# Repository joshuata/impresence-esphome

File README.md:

# Presence Sensor

An open-source, ESPHome-based room presence sensor built around the Hi-Link HLK-LD2460 mmWave radar and a Seeed Studio XIAO ESP32-S3. The base device detects human presence, even when people are sitting still, and reports it to Home Assistant. Optional add-ons extend it with ambient light and CO₂ sensing.

> **Status:** early development. Hardware and firmware are not yet finalized.

<!-- TODO: hero photo of the assembled device -->

## Features

- mmWave presence detection (HLK-LD2460)
- Native Home Assistant integration through ESPHome
- Wi-Fi setup over USB or Bluetooth (Improv), with no code editing required
- Browser-based flashing, no toolchain needed
- Over-the-air updates
- Optional add-ons:
  - Ambient light sensor
  - CO₂ sensor
- Custom PCB and 3D-printable enclosure, with source files included

## Bill of materials

### Base device

| Qty | Part | Notes |
|----:|------|-------|
| 1 | Seeed Studio XIAO ESP32-S3 | |
| 1 | Hi-Link HLK-LD2460 mmWave radar | |
| 1 | Custom PCB, assembled | Order it with assembly; see [1. PCB](#1-pcb) |
| 1 | 3D-printed enclosure | See [`hardware/enclosure`](hardware/enclosure) |
| 1 | USB-C cable + 5 V power supply | |
| 1 | PCB parts (radar sockets, Qwiic socket, LDO, passives) | Only if you assemble the PCB yourself. Full list in [`hardware/pcb/presence-pcb-bom.csv`](hardware/pcb/presence-pcb-bom.csv) |
| 4 | M2.5 screws + heat-set inserts | Length TBD with the case |

### Optional add-ons

| Add-on | Part | Notes |
|--------|------|-------|
| Ambient light | Adafruit VEML7700 Lux Sensor, STEMMA QT (5378) | Plugs into the Qwiic chain |
| CO₂ | Adafruit SCD-40 breakout (5187) | Plugs into the Qwiic chain |

## Building

### 1. PCB

The fabrication files are in [`hardware/pcb`](hardware/pcb):

| File | What it's for |
|------|---------------|
| `presence-pcb-gerbers.zip` | Gerber and drill files. Upload this to any PCB maker |
| `presence-pcb-bom.csv` | Every part on the board, with manufacturer and LCSC part numbers |
| `presence-pcb-bom-jlcpcb.csv` | Assembly BOM in JLCPCB's format |
| `presence-pcb-cpl-jlcpcb.csv` | Pick-and-place (CPL) file in JLCPCB's format |

The board has two layers and is 53.5 × 57.955 mm, 1.6 mm thick. It uses 0.2 mm minimum tracks and clearances and 0.3 mm via drills, which any standard PCB service can make. Every part is on the top side.

#### Ordering from JLCPCB with assembly

JLCPCB can build the board with everything fitted except the XIAO, which you solder yourself. The optional parts (R1, R2, J4) are left off; see [Optional parts](#optional-parts).

1. On [jlcpcb.com](https://jlcpcb.com), start a PCB order and upload `presence-pcb-gerbers.zip`. Check that it detects 2 layers and a size of about 53.5 × 58 mm.
2. Set the PCB options:
   - **Base material:** FR-4
   - **Layers:** 2
   - **PCB thickness:** 1.6 mm
   - **Surface finish:** lead-free HASL or ENIG
   - **Quantity:** however many bare boards you want
   - Leave the other options at their defaults. Some colours and finishes aren't offered with Economic assembly; the site greys those out.
3. Turn on **PCB Assembly** and set:
   - **PCBA type:** Economic
   - **Assembly side:** Top side
   - **PCBA quantity:** the number of boards to assemble. The minimum is 2.
   - **Confirm parts placement:** yes. A JLCPCB engineer checks the part orientations and sends them to you to approve before assembly, for a small fee. It's worth it until the files have been proven on a real order.
4. Upload `presence-pcb-bom-jlcpcb.csv` as the BOM and `presence-pcb-cpl-jlcpcb.csv` as the CPL (pick-and-place) file.
5. On the parts page, check that every line matched the LCSC part number in the file. There should be eight lines:
   - **Basic parts:** C1–C5, FB1
   - **Extended parts:** U2, J1, J2, J3. Each unique extended part adds a feeder-loading fee.
   - **J1 and J2:** the radar sockets are through-hole, so JLCPCB solders them by hand and adds a small through-hole fee. To solder them yourself instead, untick them and buy HCTL PM200-2-04-Z-4.3 and PM200-2-02-Z-4.3. Any substitute must be 4.3 mm tall (`pcb_socket_h`), or the radar won't line up with the case.
   - **Out-of-stock parts:** choose one with the same value, rating and footprint. For J3, use only the JST BM04B-SRSS-TB or an exact equivalent: the case is shaped around its height.
6. In the placement preview, check that every part sits on its pads and that the polarised parts point the right way:
   - **J1:** the 2×4 socket lies along its two columns of four holes. The CPL file already corrects for JLCPCB's model being drawn at 90° to the footprint
   - **U2:** pin 1
   - **J3:** the four contacts on the small pads and the mounting tabs on the two large ones
7. Add the order to your cart and check out. JLCPCB asks for a product description for customs; pick the closest one.

The Gerber zip works with any other PCB maker too. Other assembly services need their own BOM and CPL formats; build them from `presence-pcb-bom.csv`.

#### After the boards arrive

1. **XIAO ESP32-S3 (U1):** solder it flush, with its castellated edges on the pads, or on pin headers. Only the 14 edge pins are used. There's no copper under the XIAO's bottom pads, so don't solder those.
2. **Check before powering:** before powering the first board, check the radar socket pinout against a module, following [Wiring](hardware/README.md#wiring). In short: JP103 pin 1 (5 V) is the bottom pin of the column nearest the board edge.

#### Optional parts

| Ref | Part | When to fit it |
|-----|------|----------------|
| R1, R2 | 4.7 kΩ 0805 resistors (I²C pull-ups) | Only for a Qwiic breakout without its own pull-ups. The Adafruit breakouts have them |
| J4 | 1×4 2.54 mm header | To solder an I²C cable instead of using the Qwiic socket |

### 2. Enclosure

TODO: print settings (material, layer height, supports, infill) and orientation.

### 3. Assembly

TODO: mounting the PCB, radar orientation, and installing add-ons.

## Flashing

### Option A: Browser (recommended)

TODO: link to the ESP Web Tools install page. Connect the device over USB, click **Install**, then enter your Wi-Fi credentials when prompted.

### Option B: ESPHome Dashboard / CLI

Requires ESPHome TBD or newer, the first release with the [`ld2460`](https://next.esphome.io/components/sensor/ld2460/) component.

```bash
pip install esphome
esphome run firmware/presence.yaml
```

TODO: adopting the device in the ESPHome Dashboard.

## Wi-Fi setup

TODO: Improv over serial/BLE and fallback access point instructions.

## Home Assistant

TODO: discovery, exposed entities, and suggested automations.

## Enabling add-ons

TODO: how to include the add-on packages in `firmware/presence.yaml`.

## Repository layout

| Path | Contents |
|------|----------|
| `firmware/` | ESPHome configuration and add-on packages |
| `hardware/pcb/` | Autodesk Fusion PCB design and fabrication exports |
| `hardware/enclosure/` | Autodesk Fusion enclosure design and printable files |
| `docs/` | Images, wiring diagrams, web installer |

## Made for ESPHome

This project aims to meet the [Made for ESPHome](https://esphome.io/guides/made_for_esphome/) requirements. Progress against the [checklist](https://github.com/esphome/devices.esphome.io/blob/main/.github/made-for-esphome-checklist.md) is tracked in the project issues.

## Contributing

Issues and pull requests are welcome. If you use an AI coding agent, it should follow [`AGENTS.md`](AGENTS.md).

## License

- **Firmware, software, and documentation:** [GNU General Public License v3.0 or later](LICENSE) (`GPL-3.0-or-later`).
- **Hardware designs** (everything under `hardware/`: PCB, enclosure, and their fabrication exports): [CERN Open Hardware Licence v2 – Strongly Reciprocal](LICENSE-HARDWARE) (`CERN-OHL-S-2.0`).

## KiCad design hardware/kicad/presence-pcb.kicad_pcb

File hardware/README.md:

# Hardware

The Autodesk Fusion project **Presence sensor** holds the mechanical source designs; Fusion exports are kept here so they are version controlled and usable without Fusion. The main PCB is a KiCad project in this folder (see `AGENTS.md`, Hardware).

| Path | Contents |
|------|----------|
| `fusion/` | Fusion source exports (`.f3d`; `.f3z` for designs with inserted, referenced components) |
| `kicad/` | KiCad 10 project for the main PCB: schematic, board, project symbol/footprint library and build scripts |
| `pcb/` | Fabrication outputs for the main PCB: Gerber + drill zip, BOM, JLCPCB assembly files |
| `enclosure/` | Print outputs for the case (once finalized) |

## Designs

| Design | What it is |
|--------|------------|
| `ld2460 Board` | HLK-LD2460 radar: board, headers, pins, keep-outs |
| `xiao-esp32s3` | Seeed XIAO ESP32-S3: board, pin holes, USB-C, keep-out |
| `adafruit-scd40` | Adafruit SCD-40 breakout (for later case variants) |
| `adafruit-veml7700` | Adafruit VEML7700 breakout (for later case variants) |
| `presence-skeleton` | Master layout for the radar + PCB prototype. Derives the radar and XIAO models and holds every case, PCB, mount and antenna dimension |

## Changing dimensions

The dimensions you're likely to change are named user parameters, and most others are derived from them or from the component models. In Fusion, open `presence-skeleton` and go to **Modify → Change Parameters**. Edit the value in the *User Parameters* section, and everything that depends on it updates. Parameters ending in `_Ref` come from the component models; change those in the component design instead. The case derives from the skeleton, so changes made there flow through to it. The KiCad PCB takes its outline, holes and part positions from the same values (in `kicad/scripts/build_board.py`), so update the script and rebuild the board after changing a layout parameter.

Values most people will want to check before printing are **bold**.

### Layout

| Parameter | Value | Description |
|-----------|-------|-------------|
| `pcb_thickness` | 1.6 mm | Main PCB thickness |
| **`pcb_socket_h`** | 4.3 mm | Height of the 2.0 mm female sockets the radar plugs into. Set to the part you buy |
| `pcb_margin` | 2 mm | PCB extends this far beyond the radar outline |
| `pcb_hole_inset` | 3 mm | PCB edge to mounting-hole centre |
| `pcb_pin_protrusion` | 2 mm | Through-hole pin length below the PCB |
| `layout_gap_radar_xiao` | 3 mm | Gap between the radar outline and the top of the XIAO |
| `xiao_side_offset` | 10 mm | XIAO shifted right (toward the antenna) to leave room on the left for a right-angle USB-C plug |

### Case

| Parameter | Value | Description |
|-----------|-------|-------------|
| `case_wall` | 2 mm | Wall thickness |
| `case_corner_r` | 3 mm | Outer corner radius |
| `case_margin` | 1 mm | Clearance from the PCB edge to the inner wall |
| **`case_radome_t`** | 1.4 mm | Wall thickness in front of the radar (community reports for 24 GHz; verify with a range test) |
| **`case_radome_gap`** | 2 mm | Radar antenna face to the inside of the front wall (1–3 mm) |
| **`case_bay_h`** | 12.5 mm | Cable bay below the PCB; sized for a right-angle USB-C plug |
| **`tol_clearance`** | 0.2 mm | General clearance between printed parts; tune for your printer |

### Fasteners

| Parameter | Value | Description |
|-----------|-------|-------------|
| `screw_clear_d` | 2.7 mm | M2.5 clearance hole in the PCB |
| **`insert_hole_d`** | 3.6 mm | Heat-set insert hole diameter. Inserts vary by brand; use your supplier's recommendation |
| **`insert_hole_h`** | 4 mm | Heat-set insert hole depth |
| `insert_boss_d` | 6.5 mm | Boss diameter around each insert |

### Wall mount (keyholes)

The back has two keyholes on the vertical centreline. Any accessory, such as a wedge or stand, that presents two #8 pan-head screw heads (or printed studs of the same shape) at this spacing can hold the case.

| Parameter | Value | Description |
|-----------|-------|-------------|
| **`mount_head_d`** | 7.9 mm | #8 pan-head diameter (ASME B18.6.3 nominal; measure yours) |
| **`mount_head_h`** | 2.8 mm | #8 pan-head height (nominal; measure yours) |
| `mount_shank_d` | 4.2 mm | #8 shank diameter |
| `mount_keyhole_spacing` | 40 mm | Keyhole centre-to-centre |
| `mount_slot_len` | 8 mm | Slot length above each entry hole |

### Hinge

| Parameter | Value | Description |
|-----------|-------|-------------|
| **`hinge_pin_d`** | 1.75 mm | Hinge pin: a piece of 1.75 mm filament or a metal pin |
| `hinge_knuckles` | 5 | Number of hinge knuckles |
| `hinge_clearance` | 0.3 mm | Knuckle and pin clearance |

### Wi-Fi / Bluetooth antenna

The XIAO's included flexible antenna sticks flat to the inside of the right-hand side wall. Its U.FL cable makes a 180° U-bend before reaching the XIAO, to take strain off the antenna joint.

| Parameter | Value | Description |
|-----------|-------|-------------|
| `ant_len` × `ant_w` × `ant_t` | 37.5 × 17.5 × 0.25 mm | Antenna size (measured) |
| `ant_cable_len` | 60 mm | U.FL cable length (measured) |
| `ant_bend_gap` | 6 mm | Spacing of the U-bend |
| `ant_drop` | 5 mm | Antenna centre below the radar centreline |
| `xiao_ufl_from_edge`, `xiao_ufl_from_centre` | 1.72, 4.73 mm | U.FL connector position on the XIAO (from Seeed's 3D model) |

### USB cable

| Parameter | Value | Description |
|-----------|-------|-------------|
| `usb_plug_w` × `usb_plug_h` | 12 × 6.5 mm | Straight USB-C plug body (measure your cable) |
| `usb_cable_d` | 4 mm | Cable diameter |
| `usb_cable_bend_r` | 10 mm | Minimum bend radius |

### Derived values (don't edit)

| Parameter | Value | Meaning |
|-----------|-------|---------|
| `z_antenna_face` | 8.0 mm | Radar antenna face above the PCB front |
| `case_front_inner` | 10.0 mm | Inside of the front wall above the PCB front |
| `pcb_back_clear` | 6.3 mm | Space behind the PCB: the largest of pin clearance, insert depth and the depth the antenna needs |
| `case_inner_depth` | 17.9 mm | Inside depth of the case |
| `case_inner_half_w`, `case_inner_top`, `case_inner_bottom` | 27.75, 19.0, 52.455 mm | Inner case extents from the radar centre |
| `ant_path_len` | 44.2 mm | Estimated antenna cable route |
| `ant_path_slack` | 15.8 mm | Spare cable. **Must stay ≥ 0**; adjust `ant_drop` if it goes negative |

At these values the case is about 59.5 × 75.5 × 21.3 mm (W × H × D).

## Main PCB

KiCad project `kicad/presence-pcb.kicad_pro`; two layers, 53.5 × 57.955 mm, 1.6 mm. The outline, the four M2.5 holes, the radar sockets and the XIAO position come from `presence-skeleton` (radar centre = origin, PCB front facing the room). Every part is on the front; the back carries only through-hole pins and a GND pour.

### Rebuilding

```sh
cd hardware/kicad
kicad-cli sch export netlist --format kicadsexpr -o /tmp/presence.net presence-pcb.kicad_sch
"/Applications/KiCad/KiCad.app/Contents/Frameworks/Python.framework/Versions/Current/bin/python3" \
  scripts/build_board.py /tmp/presence.net      # placement, routing, pours, silkscreen
scripts/export_fab.sh                           # ERC + DRC + parity, then hardware/pcb/*
```

`build_board.py` routes with its own small grid router, so the board is reproducible from the schematic without an autorouter. The custom footprints in `presence.pretty` come from `scripts/gen_footprints.py`.

### Wiring

Nets are named after XIAO pins. These match `firmware/boards/xiao-esp32s3.yaml`.

| Net | XIAO pin | Goes to |
|-----|----------|---------|
| `D8` | D8 (TX) | LD2460 J1 pin 8, Rx2 |
| `D9` | D9 (RX) | LD2460 J1 pin 7, Tx2 |
| `D4` | D4 (SDA) | Qwiic J3 pin 3, J4 pin 3 |
| `D5` | D5 (SCL) | Qwiic J3 pin 4, J4 pin 4 |
| `5V` | 5V (VBUS) | Radar filter, Qwiic LDO. The board is powered only through the XIAO's USB-C |
| `RADAR_5V` | – | LD2460 JP103 pin 1, after FB1 + 22 µF + 100 nF |
| `QWIIC_3V3` | – | Qwiic J3/J4 pin 2, from the AP2112K LDO U2 |
| `GND` | GND | LD2460 pins 2 and 6, Qwiic pin 1 |
| `D0` `D1` `D3` `D6` `D7` `D10` | spare | Test pads TP1–TP6 (through-hole, wire-solderable). D2 is left unconnected: GPIO3 is an S3 strapping pin |

LD2460 pin numbers follow manual V1.1, Fig. 3. The PCB faces the module's component side, so the socket footprints are mirrored relative to that photo: on the PCB, JP103 pin 1 (5 V) is the bottom pin of the column nearest the board edge, and J1 pin 5 is the bottom pin of the inner column. **Check the first board against a module before powering it.**

### Parts

`pcb/presence-pcb-bom.csv` lists every part. `pcb/presence-pcb-bom-jlcpcb.csv` and `pcb/presence-pcb-cpl-jlcpcb.csv` are for JLCPCB assembly: they include the SMD parts, the radar sockets and the Qwiic socket, and leave out the XIAO (hand-soldered) and the DNP parts. Check the part rotations in JLCPCB's placement preview before ordering.

- **XIAO (U1):** solder it flush (castellated edges onto the pads) or on pin headers. The footprint uses the 14 edge pins only; there is no copper on the front under the XIAO's bottom pads.
- **Radar sockets (J1, J2):** 2.0 mm female, 4.3 mm tall (`pcb_socket_h`). The radar plugs in with its antennas facing out.
- **Qwiic (J3):** JST SH BM04B-SRSS-TB, top entry (the cable plugs in from the front), body centre at (-22.8, -27.5) skeleton coordinates, 3.45 mm in from the left PCB edge. The header is 4.25 mm tall and the SHR-04V-S plug housing is 5 mm tall (JST SH catalogue eSH, pp. 2–3); JST gives no mated height, so measure a real cable before finalizing the cover. J4 is the same bus on 2.54 mm pads for a soldered cable or header. Both are fed 3.3 V by a dedicated AP2112K-3.3 LDO (U2), separate from the XIAO's 3V3.
- **I²C pull-ups (R1, R2, DNP):** the Adafruit breakouts have their own. Fit 4.7 kΩ only for a breakout without pull-ups.
- **Antenna side:** no copper pour within 5.5 mm of the right edge, next to the antenna on the side wall.

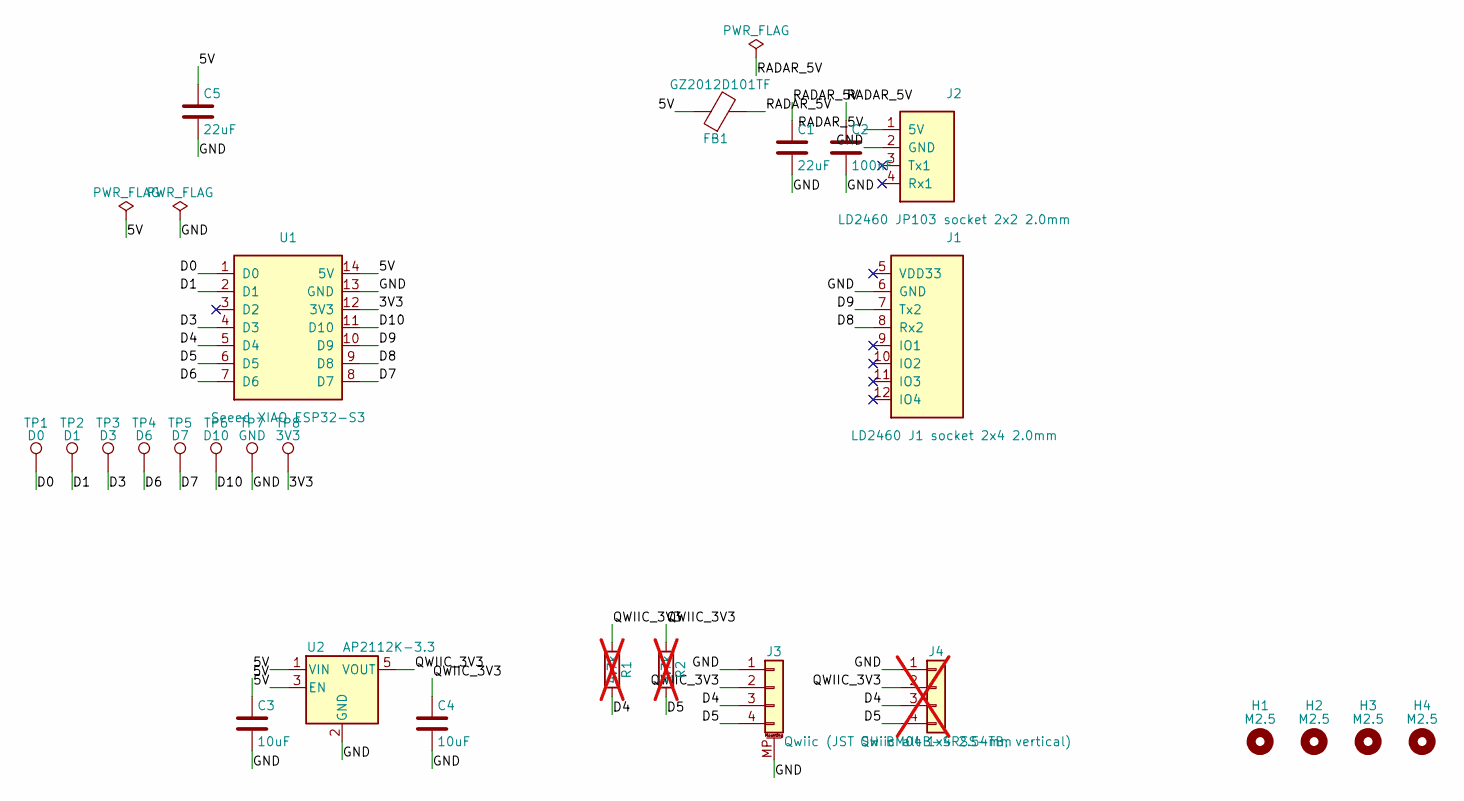
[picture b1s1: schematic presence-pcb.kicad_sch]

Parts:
C1, C5: 22uF; C_0805_2012Metric; MPN CL21A226MAQNNNE; LCSC C45783
C2: 100nF; C_0805_2012Metric; MPN CC0805KRX7R9BB104; LCSC C49678
C3, C4: 10uF; C_0805_2012Metric; MPN CL21A106KAYNNNE; LCSC C15850
FB1: GZ2012D101TF; L_0805_2012Metric; MPN GZ2012D101TF; LCSC C1015
H1, H2, H3, H4: M2.5; MountingHole_2.7mm_M2.5
J1: LD2460 J1 socket 2x4 2.0mm; LD2460_J1_Socket_2x04_P2.00mm; MPN PM200-2-04-Z-4.3; LCSC C2906072
J2: LD2460 JP103 socket 2x2 2.0mm; LD2460_JP103_Socket_2x02_P2.00mm; MPN PM200-2-02-Z-4.3; LCSC C2906070
J3: Qwiic (JST SH BM04B-SRSS-TB, vertical); JST_SH_BM04B-SRSS-TB_1x04-1MP_P1.00mm_Vertical; MPN BM04B-SRSS-TB(LF)(SN); LCSC C160390
J4: Qwiic alt 1x4 2.54mm; PinHeader_1x04_P2.54mm_Vertical; MPN 1x4 2.54 mm pin header; not fitted
R1, R2: 4.7k; R_0805_2012Metric; MPN 0805W8F4701T5E; LCSC C17673; not fitted
TP1: D0; TestPoint_THTPad_D1.5mm_Drill0.7mm
TP2: D1; TestPoint_THTPad_D1.5mm_Drill0.7mm
TP3: D3; TestPoint_THTPad_D1.5mm_Drill0.7mm
TP4: D6; TestPoint_THTPad_D1.5mm_Drill0.7mm
TP5: D7; TestPoint_THTPad_D1.5mm_Drill0.7mm
TP6: D10; TestPoint_THTPad_D1.5mm_Drill0.7mm
TP7: GND; TestPoint_THTPad_D1.5mm_Drill0.7mm
TP8: 3V3; TestPoint_THTPad_D1.5mm_Drill0.7mm
U1: Seeed XIAO ESP32-S3; XIAO_ESP32S3_EdgePins; MPN XIAO ESP32S3
U2: AP2112K-3.3; SOT-23-5; MPN AP2112K-3.3TRG1; LCSC C51118

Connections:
/3V3: TP8.1, U1.12 (3V3)
/5V: C3.1, C5.1, FB1.1, U1.14 (5V), U2.1 (VIN), U2.3 (EN)
/D0: TP1.1, U1.1 (D0)
/D1: TP2.1, U1.2 (D1)
/D3: TP3.1, U1.4 (D3)
/D4: J3.3, J4.3, R1.2, U1.5 (D4)
/D5: J3.4, J4.4, R2.2, U1.6 (D5)
/D6: TP4.1, U1.7 (D6)
/D7: TP5.1, U1.8 (D7)
/D8: J1.8 (Rx2), U1.9 (D8)
/D9: J1.7 (Tx2), U1.10 (D9)
/D10: TP6.1, U1.11 (D10)
/GND: C1.2, C2.2, C3.2, C4.2, C5.2, J1.6 (GND), J2.2 (GND), J3.1, J3.MP (MountPin), J4.1, TP7.1, U1.13 (GND), U2.2 (GND)
/QWIIC_3V3: C4.1, J3.2, J4.2, R1.1, R2.1, U2.5 (VOUT)
/RADAR_5V: C1.1, C2.1, FB1.2, J2.1 (5V)

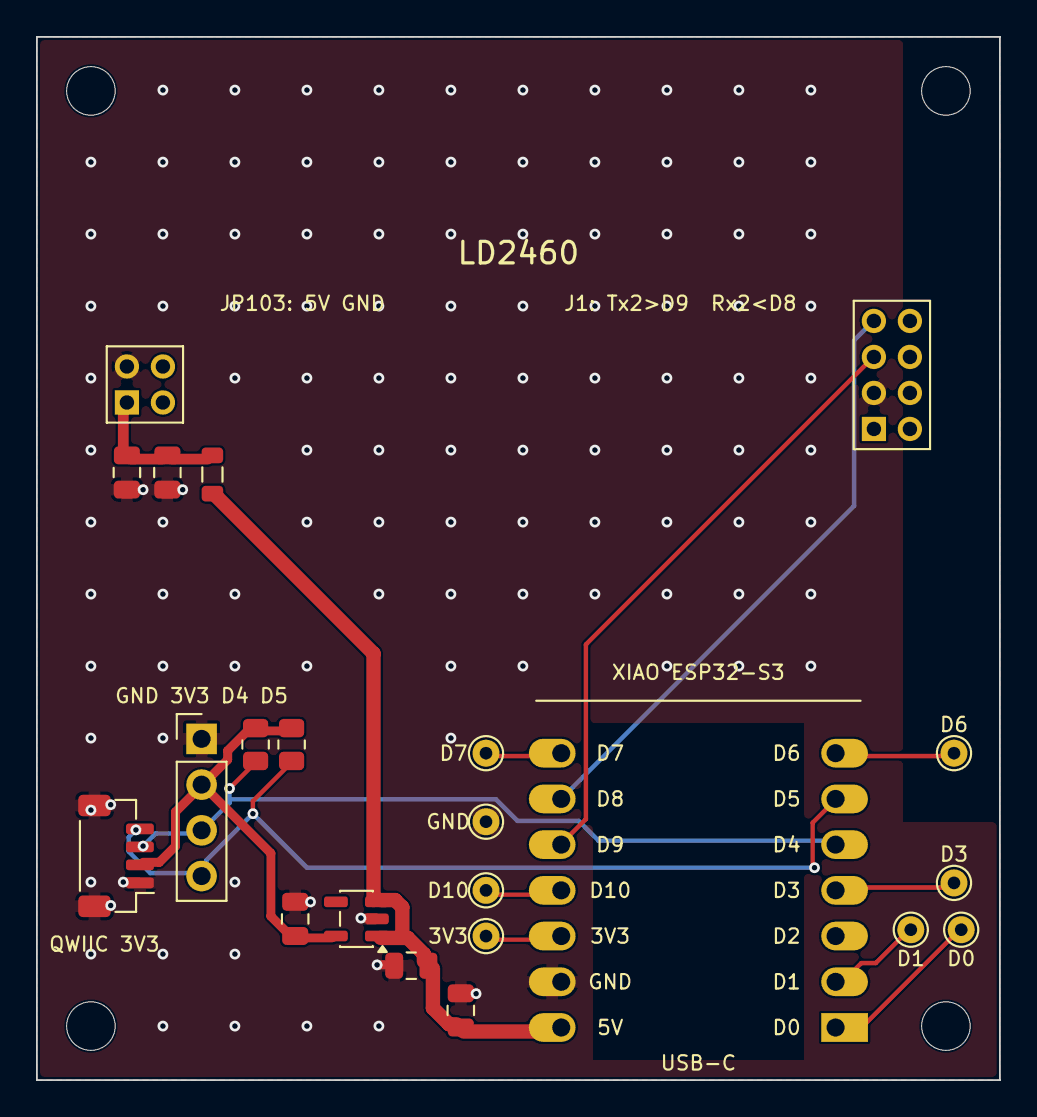
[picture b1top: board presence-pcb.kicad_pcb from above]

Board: 2 copper layers, 53.5 x 58.0 mm, 26 parts (0 on the bottom side), 15 nets.

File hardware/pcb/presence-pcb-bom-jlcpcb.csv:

Comment,Designator,Footprint,LCSC Part #
22uF,"C1,C5",C_0805_2012Metric,C45783
100nF,C2,C_0805_2012Metric,C49678
10uF,"C3,C4",C_0805_2012Metric,C15850
GZ2012D101TF,FB1,L_0805_2012Metric,C1015
LD2460 J1 socket 2x4 2.0mm,J1,LD2460_J1_Socket_2x04_P2.00mm,C2906072
LD2460 JP103 socket 2x2 2.0mm,J2,LD2460_JP103_Socket_2x02_P2.00mm,C2906070
"Qwiic (JST SH BM04B-SRSS-TB, vertical)",J3,JST_SH_BM04B-SRSS-TB_1x04-1MP_P1.00mm_Vertical,C160390
AP2112K-3.3,U2,SOT-23-5,C51118
